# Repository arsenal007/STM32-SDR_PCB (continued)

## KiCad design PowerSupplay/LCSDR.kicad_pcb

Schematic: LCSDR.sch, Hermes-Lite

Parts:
C1, C2, C4, C17, C46, C79, C95: 10uF; Universal_C_Radial_D5_L11_P2_tantal
C3, C5, C6, C14, C15, C16, C18, C22, C29, C31, C35, C47, C53, C68, C70, C72, C73, C74, C76, C78, C82, C87, C89, C94, C96: 100nF; C_1206_0603
C7, C8, C9, C13, C52: 10uF; CP_Tantalum_Case-A_EIA-3216-18_Hand
C10, C21, C24, C25, C40, C54, C67, C81, C91, C100, C101, C102, C103: 1uF; C_1206_0603
C11, C12: 22pF; C_1206_0603
C19, C30, C41, C48, C80: 10uF 16v; CP_Tantalum_Case-A_EIA-3216-18_Hand
C20, C77, C83, C92: 100uF; C_Radial_D5_L11_P2.5
C23, C33, C43, C51: 27nF; C_1206_0603
C26: 120pF; C_0603_HandSoldering
C27, C28: 270pF; C_1206_0603
C32, C36, C39: 680pF; C_0603_HandSoldering
C34, C56, C86, C93, C104, C105, C106, C107, C108, C110, C111: 15nF; C_0603_HandSoldering
C37, C38, C45, C49: 820pF; C_0603_HandSoldering
C42: 47uF; CP_Elec_6.3x7.7
C44, C61, C65: 360pF; C_0603_HandSoldering
C50, C62, C63: 33pF; C_0603_HandSoldering
C55, C98: 1000uF; CP_Radial_D8.0mm_P3.50mm
C57, C97: 180pF; C_0603_HandSoldering
C58, C66: 6.8uF; CP_Tantalum_Case-A_EIA-3216-18_Hand
C59, C64: 10n; C_1206_0603
C60, C69: 390p; C_0603_HandSoldering
C71: 1n; C_1206_0603
C75: 330uF; C_Radial_D10_L13_P5
C84, C85, C88, C90: 4.7uF; C_0603_HandSoldering
C109: 15n; C_0603_HandSoldering
CON1: +13,8v; BARREL_JACK
D1: LL4148; D_MiniMELF_Handsoldering
D11: LED; LED_D5.0mm
D12: WE-TVS824011; SOT-23-5_HandSoldering
J2: LINE OUT; audio_jack_3_5mm_PJ307
K1: LU-12; Relay_SPDT_HJR-4102
L1, L6, L24, L26: 100uH; Resistor_Horizontal_RM10mm
L2: 4.7uH; Choke_CD54
L3, L4, L5, L10, L22, L25: 47uH; Resistor_Horizontal_RM10mm
L7, L20, L21: 470nH; R_1210_HandSoldering
L8, L9: 220nH; R_1210_HandSoldering
L11: 4.7uH; R_1210_HandSoldering
L12, L13: 472K; Resistor_Horizontal_RM10mm
L14, L15, L16: 2.2uH; R_1210_HandSoldering
L17, L18, L19: 1uH; R_1210_HandSoldering
L23: 0.47uH; R_1210_HandSoldering
P1: BNC; BNC_Socket_TYCO-AMP
P2: SPI; Pin_Header_Straight_2x03_Pitch2.54mm
P3: USB_OTG; USB_Mini-B
P4: PA_TX; Pin_Header_Straight_1x02_Pitch2.54mm
P5: ENCODER; Pin_Header_Straight_1x04_Pitch2.54mm
P10, P11, P12, P13: CONN_01X01; MountingHole_3.2mm_M3_ISO7380_Pad
Q1: IRF510N; TO-220_Horizontal_Reversed
Q2: MMBT2222LT1G; SOT-23_Handsoldering
Q3: BFG135; SOT-223
Q4: PMBT2907; SOT-23_Handsoldering
Q5, Q6: PMBT2222; SOT-23_Handsoldering
R1, R2, R9, R10, R18, R21, R26, R27: 3k 1%; R_0603_HandSoldering
R3, R5, R22, R25, R39, R45: 1k 1%; R_0603_HandSoldering
R4, R23: 270R 1%; R_0603_HandSoldering
R6, R19, R28, R29, R30, R35: 10k; R_1206_0603
R7, R8, R62, R70: 1k; R_1206_0603
R11, R12, R15, R16: 510R; R_1206_0603
R13, R20: 47R; R_1206_0603
R14, R50, R65: 10k; R_0603_HandSoldering
R17, R24, R33, R36: 20R; R_1206_0603
R31: 82R; R_1206_0603
R32: 33R; R_2512_HandSoldering
R34, R58, R59: k91; R_1206_0603
R37, R54: 13R; R_1206_0603
R38: 20; R_0603_HandSoldering
R40, R42, R43, R46, R47: 4.7k 1%; R_0603_HandSoldering
R41: 51; R_0603_HandSoldering
R44, R49: 15; R_0603_HandSoldering
R48: 4k75; R_0603_HandSoldering
R52, R53: 82; R_0603_HandSoldering
R56: 33R; R_1206_0603
R57: 5R1; R_1206_0603
R60: k56; R_1206_0603
R61, R64: 2.2k; R_Axial_DIN0204_L3.6mm_D1.6mm_P2.54mm_Vertical
R63: k510; R_1206_0603
R66: 1k; R_0603_HandSoldering
R67: 1k5; R_1206_0603
R68, R69: 2k2; R_1206_0603
R71, R74: 1R; R_0603_HandSoldering
R72: 4.7k; R_1206_0603
R73: 330; R_1206_0603
RV1: 5k; Potentiometer_Trimmer_Bourns_3296W
T1: 1:4; TRANSF1_4
T2: 1_9; HF1_9
U1, U8: MC33179DR2G; SOIC-14_3.9x8.7mm_Pitch1.27mm
U2, U25, U26: PE4259ds; SOT-363_SC-70-6_Handsoldering
U3, U10: 74LVC1G3157; SOT-23-6_Handsoldering
U5: LD1117v25; SOT-223
U6, U14: 74HC4053; SOIC-16_3.9x9.9mm_Pitch1.27mm
U7, U11: SN74LVC1G00DCKR; SOT-353_SC-70-5_Handsoldering
U9: 74LCX574; SSOP-20_5.3x7.2mm_Pitch0.65mm
U15: L78M09; TO-252-2_Rectifier
U18: Si570; Oscillator_SMD_SI570_SI571_HandSoldering
U27: LM78L06ACZ; TO-92_Inline_Wide
Y5: 8Mhz; Crystal_HC49-U_Vertical

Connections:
/0: U3.6 (S), U9.6 (D4), U9.16 (Q3)
/0_1: R17.1, U3.3 (Y0)
/0_2: R18.1, U1.3 (+), U14.1 (Y1)
/0_3: R47.2, U8.8, U14.2 (Y0)
/2,75V: C82.1, C83.1, L4.1, R16.1, U5.2 (VO), U5.4 (VO)
/90: U9.5 (D3), U9.17 (Q2), U10.6 (S)
/90_1: R33.1, U10.3 (Y0)
/90_2: R10.2, U1.10 (+), U6.1 (Y1)
/90_3: R42.2, U6.2 (Y0), U8.14
/180_1: R24.1, U3.1 (Y1)
/180_2: R27.2, U1.5 (+), U14.3 (Z0)
/180_3: C69.1, R46.1, R48.1, U8.7, U14.5 (Z0)
/270_1: R36.1, U10.1 (Y1)
/270_2: R1.1, U1.12 (+), U6.3 (Z0)
/270_3: C60.1, R40.2, R43.2, U6.5 (Z0), U8.1
GND: C1.2, C2.2, C3.2, C4.2, C5.2, C6.2, C7.2, C10.1, C11.2, C12.2, C13.2, C14.2, C17.2, C18.2, C20.2, C21.2, C22.2, C23.2, C24.1, C25.1, C27.1, C28.1, C31.2, C33.2, C34.1, C36.1, C37.1, C38.1, C39.1, C40.1, C42.2, C43.2, C45.1, C46.2, C47.2, C49.1, C51.2, C52.2, C53.2, C54.1, C55.2, C56.1, C59.2, C61.1, C62.1, C63.1, C64.2, C65.1, C67.1, C68.2, C73.2, C74.2, C75.2, C76.2, C77.2, C78.2, C79.2, C80.2, C81.1, C82.2, C83.2, C84.1, C85.1, C87.2, C88.1, C90.1, C91.1, C92.2, C97.1, C98.2, C100.1, C101.1, C102.1, C103.1, C104.1, C105.1, C106.1, C107.1, C108.1, C109.1, C110.1, C111.2, CON1.2, CON1.3, D11.1 (K), J2.1 (T), L8.2, L9.2, L14.2, L15.2, L17.2, L18.2, L20.2, L21.2, L24.2, P1.2 (Ext), P2.6, P4.2, P5.4, P11.1, P12.1, P13.1, Q1.3 (S), Q2.2 (E), Q5.2 (E), Q6.2 (E), R6.2, R8.2, R11.1, R15.2, R28.2, R29.2, R30.2, R31.2, R35.2, R37.2, R52.1, R53.1, R54.2, R58.2, R59.2, R67.2, RV1.2, RV1.3, U1.11 (V-), U2.2 (GND), U3.2 (GND), U6.6 (Inh), U6.7 (VEE), U6.8 (VSS), U7.3 (GND), U8.11 (V-), U9.1 (OE), U9.7 (D5), U9.8 (D6), U9.9 (D7), U9.10 (GND), U10.2 (GND), U11.3 (GND), U14.6 (Inh), U14.7 (VEE), U14.8 (VSS), U15.2 (GND), U18.3 (GND), U25.2 (GND), U26.2 (GND), U27.2 (GND); also elsewhere on the board
unnamed: C1.1, C6.1, C7.1, R1.2, R2.1, R10.1, R11.2, R12.1, R18.2, R21.1, R27.1, U8.3 (+), U8.5 (+), U8.10 (+), U8.12 (+)
unnamed: C2.1, C5.1, L3.1, R12.2, U1.4 (V+)
unnamed: C8.1, R13.1
unnamed 19: C8.2; also elsewhere on the board
unnamed: C9.1, R20.1
unnamed 21: C9.2; also elsewhere on the board
unnamed 22: C11.1, Y5.2; also elsewhere on the board
unnamed 23: C12.1, Y5.1; also elsewhere on the board
unnamed: C13.1, C14.1, L5.2, R15.1, R16.2
unnamed: C15.1, C16.1, C29.1, K1.1 (C1), K1.12
unnamed: C15.2, C16.2, C29.2, P1.1 (In), R6.1, R28.1, R29.1, R30.1
unnamed: C19.1, U6.15 (Y)
unnamed: C19.2, C23.1, R17.2
unnamed 29: C20.1, C31.1, L25.2; also elsewhere on the board
unnamed: C21.1, C22.1, L4.2, L22.1, U3.5 (Vcc), U10.5 (Vcc)
unnamed: C26.1, L7.2
unnamed 32: C26.2, C28.2, L9.1; also elsewhere on the board
unnamed 33: C27.2, L7.1, L8.1; also elsewhere on the board
unnamed: C30.1, U6.4 (Z)
unnamed: C30.2, C33.1, R24.2
unnamed: C32.1, L11.2
unnamed 37: C32.2, C38.2, C39.2, L15.1; also elsewhere on the board
unnamed: C34.2, C56.2, Q2.3 (C), R14.2, U6.9 (C), U6.10 (B), U6.11 (A), U14.9 (C), U14.10 (B), U14.11 (A)
unnamed 39: C35.1; also elsewhere on the board
unnamed: C35.2, L5.1, U3.4 (Z), U10.4 (Z)
unnamed 41: C36.2, C37.2, L11.1, L14.1; also elsewhere on the board
unnamed: C40.2, C42.1, C54.2, C67.2, L2.1, T1.3
unnamed: C41.1, U14.15 (Y)
unnamed: C41.2, C43.1, R33.2
unnamed: C44.1, C50.1, L16.2
unnamed 46: C44.2, C49.2, C50.2, L18.1; also elsewhere on the board
unnamed 47: C45.2, L16.1, L17.1; also elsewhere on the board
unnamed: C46.1, C47.1, L22.2, R7.1, U7.5 (VCC), U9.20 (VCC), U11.5 (VCC)
unnamed: C48.1, U14.4 (Z)
unnamed: C48.2, C51.1, R36.2
unnamed: C52.1, C53.1, L10.2, U8.4 (V+)
unnamed: C57.1, L19.2
unnamed 53: C57.2, C63.2, C65.2, L21.1; also elsewhere on the board
unnamed: C58.1, R39.1
unnamed: C58.2, C59.1, L12.1
unnamed: C60.2, R39.2, R43.1, U8.2 (-)
unnamed 57: C61.2, C62.2, L19.1, L20.1; also elsewhere on the board
unnamed: C64.1, C66.2, L13.1
unnamed: C66.1, R45.1
unnamed: C69.2, R45.2, R46.2, U8.6 (-)
unnamed: C70.1, L23.1
unnamed: C70.2, Q3.4 (C), T2.1
unnamed: C71.1, R7.2, R8.1, U11.1, U11.2
unnamed: C71.2, U18.4 (CLK+)
unnamed: C72.1, T2.4, T2.5
unnamed: C72.2, Q1.1 (G), R35.1, R56.1
unnamed: C73.1, C80.1, L26.1, R50.1, R61.1, R64.1, U18.6 (VDD)
unnamed: C76.1, C77.1, C78.1, C79.1, L1.1, L3.2, L10.1, L25.1, U5.3 (VI), U15.3 (OUT)
unnamed: C81.2, C88.2, C92.1, L6.2, R32.1, U27.3 (IN)
unnamed: C84.2, C85.2, R32.2, T2.6
unnamed: C86.1, U2.1 (RF1)
unnamed: C86.2, R57.1, R59.1
unnamed: C87.1, Q4.3 (C), R62.2, R63.2, R65.1
unnamed 74: C89.1; also elsewhere on the board
unnamed: C89.2, U26.5 (RFC)
unnamed: C90.2, Q4.2 (E), R67.1, U27.1 (OUT)
unnamed: C93.2, D1.2 (A), K1.8, Q6.3 (C)
unnamed 78: C94.1, C95.1, D12.5 (VDD), R72.1, R73.1; also elsewhere on the board
unnamed 79: C94.2, C95.2, C96.2, D12.2 (GND), P3.5 (GND), P3.6 (shield); also elsewhere on the board
unnamed 80: C96.1; also elsewhere on the board
unnamed 81: C97.2; also elsewhere on the board
unnamed 82: C104.2; also elsewhere on the board
unnamed 83: C105.2, U25.4 (CTRL), U26.4 (CTRL); also elsewhere on the board
unnamed 84: C106.2; also elsewhere on the board
unnamed 85: C107.2; also elsewhere on the board
unnamed 86: C108.2; also elsewhere on the board
unnamed 87: C109.2, R68.2; also elsewhere on the board
unnamed 88: C110.2, R19.2; also elsewhere on the board
unnamed 89: C111.1, R69.1; also elsewhere on the board
unnamed: D11.2 (A), R70.2
unnamed 92: D12.3 (I/O1), P3.3 (D+); also elsewhere on the board
unnamed 93: D12.4 (I/O2), P3.2 (D-); also elsewhere on the board
unnamed 94: P5.3; also elsewhere on the board
unnamed 95: P2.4; also elsewhere on the board
unnamed 96: P2.1; also elsewhere on the board
unnamed 97: P2.3; also elsewhere on the board
unnamed 98: R70.1; also elsewhere on the board
unnamed 99: P4.1; also elsewhere on the board
unnamed 100: R64.2, U18.7 (SDA); also elsewhere on the board
unnamed 101: R61.2, U18.8 (SCL); also elsewhere on the board
unnamed 102: P2.5; also elsewhere on the board
unnamed 105: P5.2; also elsewhere on the board
unnamed: J2.2 (R), J2.3 (RN), L13.2
unnamed: J2.4 (SN), J2.5 (S), L12.2
unnamed: K1.6 (T1), T1.2
unnamed: K1.7 (R1), L24.1, U2.3 (RF2)
unnamed: L23.2, R34.2
unnamed: P3.1 (VCC), R73.2
unnamed: Q1.2 (D), T1.1, T1.4
unnamed: Q2.1 (B), R19.1
unnamed: Q3.1 (E), R54.1
unnamed: Q3.2 (B), R34.1, R57.2, R58.1, R60.1
unnamed: Q3.3 (C), R37.1
unnamed: Q4.1 (B), R65.2, R66.1
unnamed: Q5.1 (B), R68.1
unnamed: Q5.3 (C), R66.2
unnamed: Q6.1 (B), R69.2
unnamed: R2.2, R3.1, R4.1, U1.13 (-)
unnamed: R3.2, R5.2, U1.14
unnamed: R4.2, R5.1, R9.1, U1.9 (-)
unnamed: R9.2, R13.2, U1.8
unnamed: R20.2, R26.2, U1.7
unnamed: R21.2, R22.1, R23.1, U1.2 (-)
unnamed: R22.2, R25.2, U1.1
unnamed: R23.2, R25.1, R26.1, U1.6 (-)
unnamed: R31.1, U5.1 (GND)
unnamed: R38.1, R41.1
unnamed: R38.2, R44.2, U25.1 (RF1)
unnamed: R40.1, R42.1, U8.13 (-)
unnamed: R41.2, R49.2, U26.1 (RF1)
unnamed: R44.1, R52.2
unnamed: R47.1, R48.2, U8.9 (-)
unnamed: R49.1, R53.2
unnamed: R50.2, U18.2 (OE)
unnamed: R56.2, R63.1, RV1.1
unnamed: R60.2, R62.1
unnamed 140: R71.2, R74.2; also elsewhere on the board
unnamed 141: R72.2; also elsewhere on the board
unnamed: T2.2, T2.3
unnamed: U2.5 (RFC), U25.5 (RFC)
unnamed: U7.1, U7.2, U9.4 (D2), U9.18 (Q1)
unnamed: U7.4, U9.2 (D0)
unnamed: U9.3 (D1), U9.19 (Q0)
unnamed: U9.11 (Cp), U11.4
unnamed: U25.3 (RF2), U26.3 (RF2)
VDD: C3.1, C4.1, C17.1, C18.1, L1.2, R14.1, U6.16 (VDD), U14.16 (VDD)

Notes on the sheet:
80M
40M
20M
17..10M
10dB

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
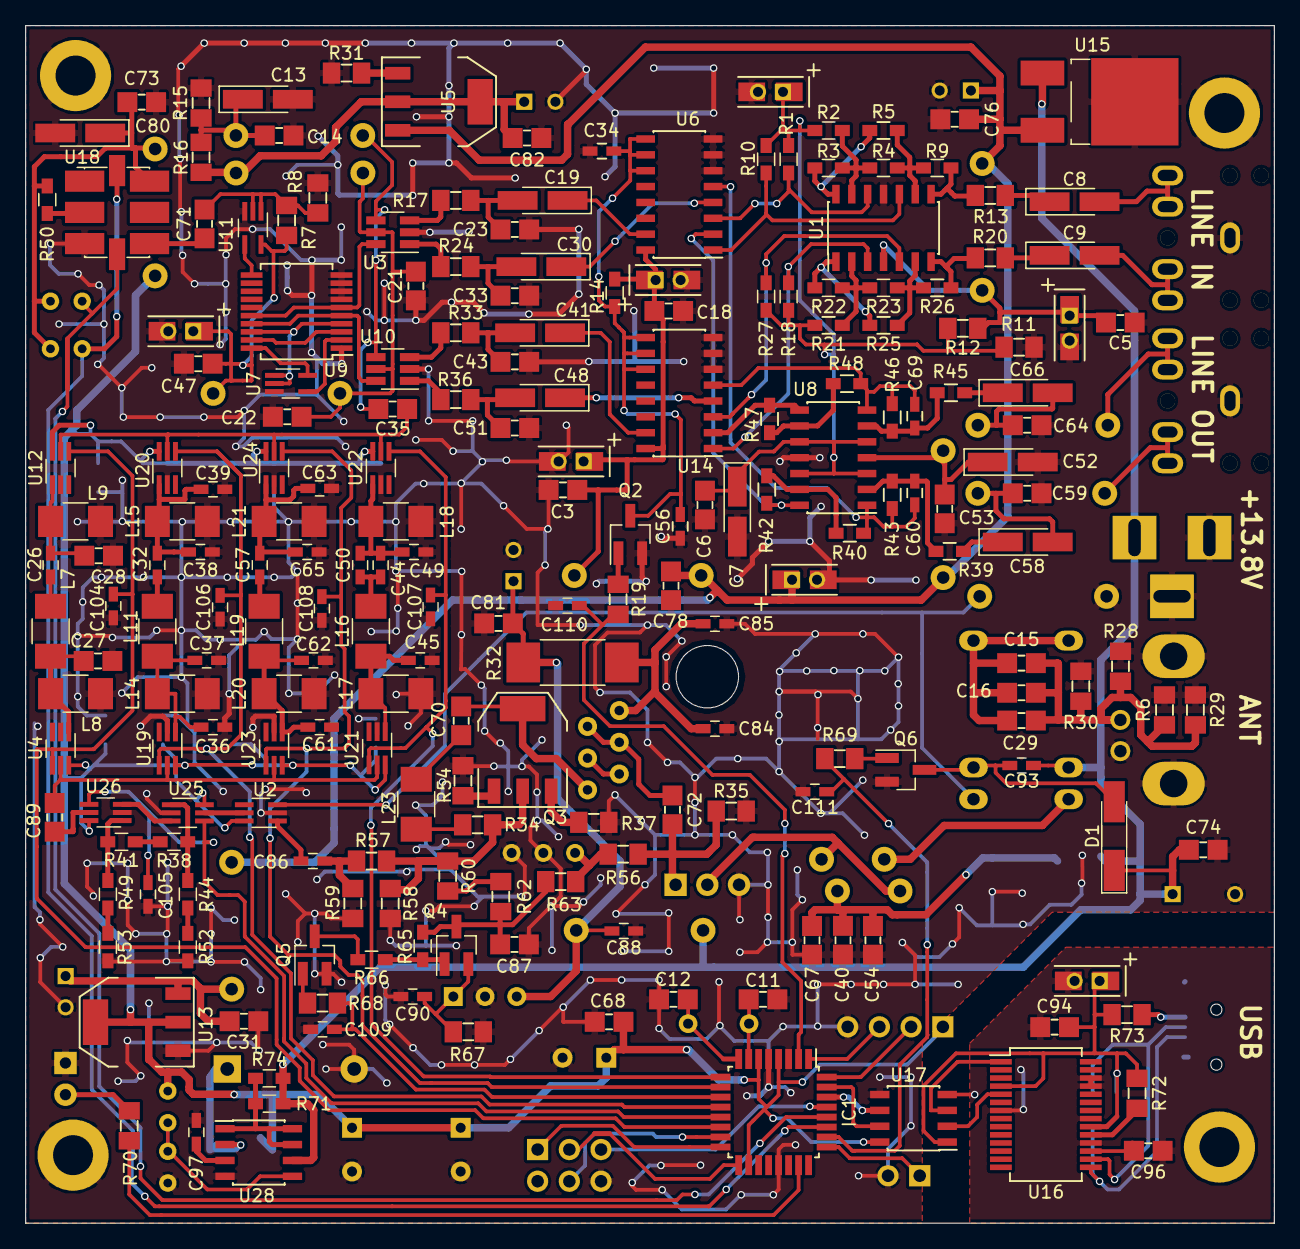
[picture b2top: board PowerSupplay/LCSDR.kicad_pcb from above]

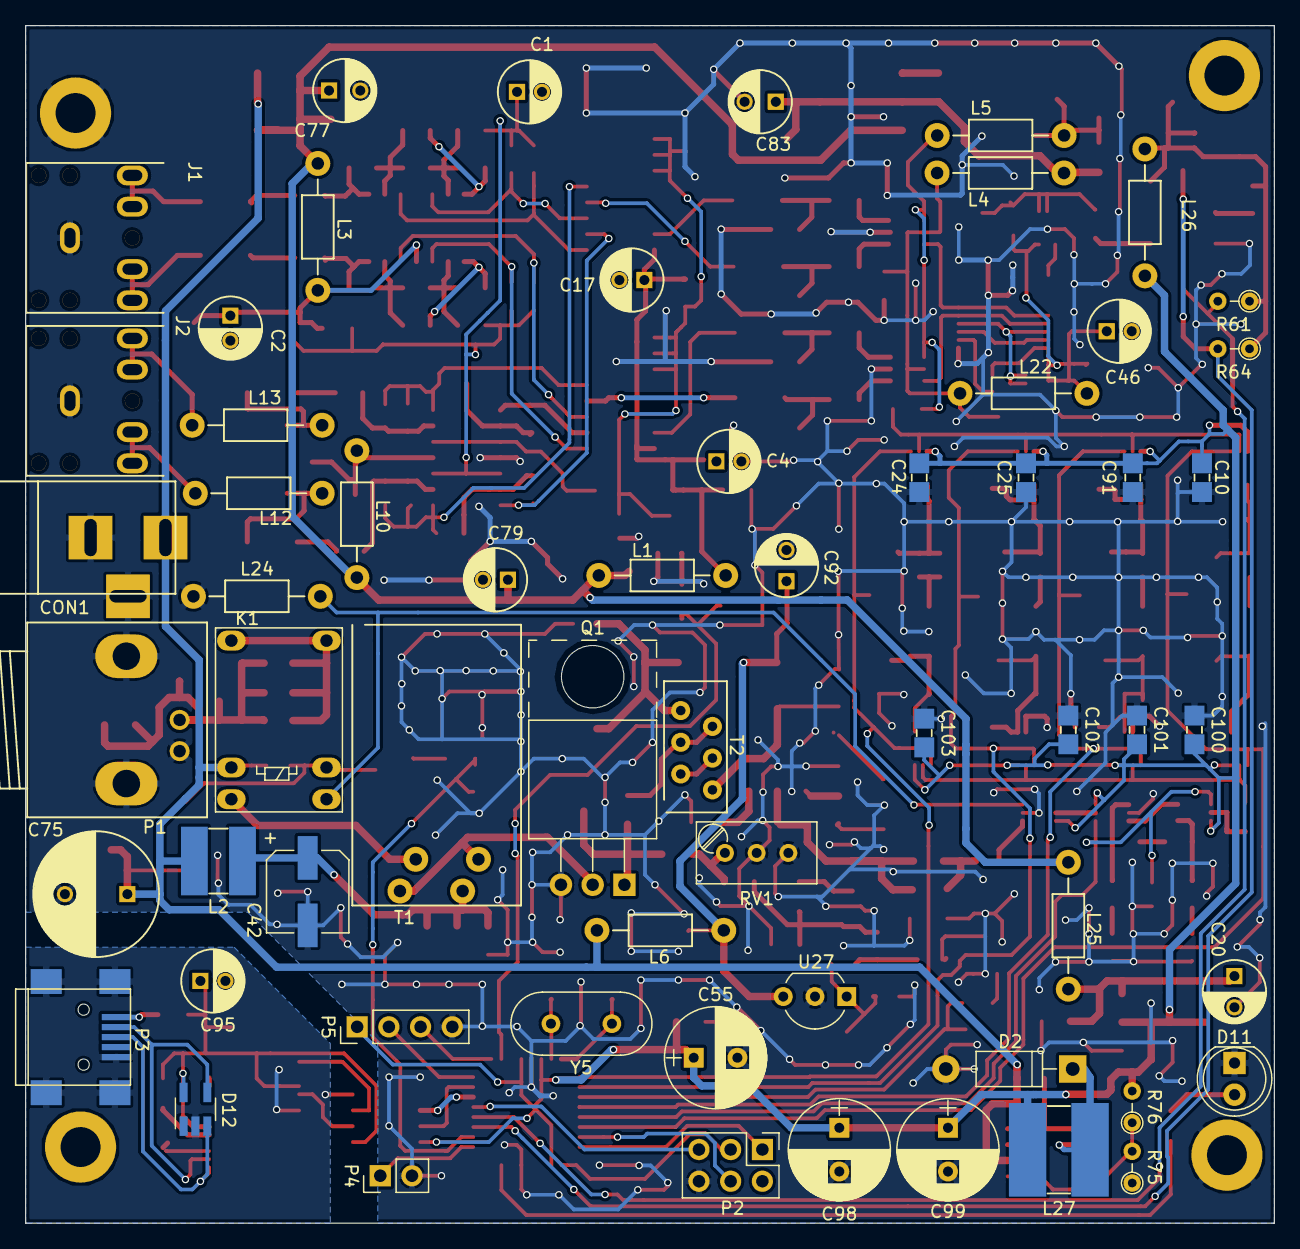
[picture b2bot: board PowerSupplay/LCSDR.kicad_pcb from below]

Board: 2 copper layers, 100.0 x 95.9 mm, 268 parts (60 on the bottom side), 155 nets.

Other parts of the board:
C99: 1000uF; CP_Radial_D8.0mm_P3.50mm
D2: 1N5819; D_DO-41_SOD81_P10.16mm_Horizontal
IC1: ATMEGA328-A; TQFP-32_7x7mm_Pitch0.8mm
J1: LINE IN; audio_jack_3_5mm_PJ307
L27: 33uH; Choke_CD75
R75: 11k; R_Axial_DIN0204_L3.6mm_D1.6mm_P2.54mm_Vertical
R76: 18k; R_Axial_DIN0204_L3.6mm_D1.6mm_P2.54mm_Vertical
U4, U12, U19, U20, U21, U22, U23, U24: PE4259ds; SOT-363_SC-70-6_Handsoldering
U13: LD1117v33; SOT-223
U16: FT232RL; SSOP-28_5.3x10.2mm_Pitch0.65mm
U17: ADuM1201BR; SOIC-8_3.9x4.9mm_Pitch1.27mm
U28: MC34063; SOIC-8_3.9x4.9mm_Pitch1.27mm

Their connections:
GND: C99.2, D2.2, IC1.3, IC1.5, IC1.21, J1.1, R75.1, U4.2, U12.2, U13.1, U17.5, U19.2, U20.2, U21.2, U22.2, U23.2, U24.2, U28.4; also elsewhere on the board
unnamed 19: J1.2, J1.3; also elsewhere on the board
unnamed 21: J1.4, J1.5; also elsewhere on the board
unnamed 22: IC1.7; also elsewhere on the board
unnamed 23: IC1.8; also elsewhere on the board
unnamed 29: U13.3; also elsewhere on the board
unnamed 32: U12.1; also elsewhere on the board
unnamed 33: U4.1; also elsewhere on the board
unnamed 37: U20.1; also elsewhere on the board
unnamed 39: U12.5, U20.5, U22.5, U24.5; also elsewhere on the board
unnamed 41: U19.1; also elsewhere on the board
unnamed 46: U22.1; also elsewhere on the board
unnamed 47: U21.1; also elsewhere on the board
unnamed 53: U24.1; also elsewhere on the board
unnamed 57: U23.1; also elsewhere on the board
unnamed 74: U4.5, U19.5, U21.5, U23.5; also elsewhere on the board
unnamed 78: U16.4, U16.20, U17.1; also elsewhere on the board
unnamed 79: U16.7, U16.18, U16.21, U16.25, U16.26, U17.4; also elsewhere on the board
unnamed 80: U16.17; also elsewhere on the board
unnamed 81: U28.3; also elsewhere on the board
unnamed 82: IC1.14, U4.4, U12.4; also elsewhere on the board
unnamed 83: IC1.13; also elsewhere on the board
unnamed 84: IC1.12, U19.4, U20.4; also elsewhere on the board
unnamed 85: IC1.9, U21.4, U22.4; also elsewhere on the board
unnamed 86: IC1.10, U23.4, U24.4; also elsewhere on the board
unnamed 87: IC1.11; also elsewhere on the board
unnamed 88: IC1.2; also elsewhere on the board
unnamed 89: IC1.26; also elsewhere on the board
unnamed: D2.1, L27.1, U28.2
unnamed 92: U16.15; also elsewhere on the board
unnamed 93: U16.16; also elsewhere on the board
unnamed 94: IC1.1; also elsewhere on the board
unnamed 95: IC1.15; also elsewhere on the board
unnamed 96: IC1.16; also elsewhere on the board
unnamed 97: IC1.17; also elsewhere on the board
unnamed 98: IC1.23; also elsewhere on the board
unnamed 99: IC1.25; also elsewhere on the board
unnamed 100: IC1.27; also elsewhere on the board
unnamed 101: IC1.28; also elsewhere on the board
unnamed 102: IC1.29; also elsewhere on the board
unnamed: IC1.30, U17.6
unnamed: IC1.31, U17.7
unnamed 105: IC1.32; also elsewhere on the board
unnamed 140: U28.1, U28.7, U28.8; also elsewhere on the board
unnamed 141: U16.19; also elsewhere on the board
unnamed: R75.2, R76.1, U28.5
unnamed: U16.1, U17.3
unnamed: U16.5, U17.2

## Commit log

2020-04-18 TODO: power supplay connector
2020-04-30 first module
2020-04-30 add I2S_CLKIN_MCU
2020-05-13 PCB almost ready, needs some GND vias
2020-05-13 edit
2020-05-14 production
2020-06-30 PCB for 98.304Mhz generator
